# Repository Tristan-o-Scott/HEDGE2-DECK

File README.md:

# HEDGE2-DECK
DECK board for HEDGE-2

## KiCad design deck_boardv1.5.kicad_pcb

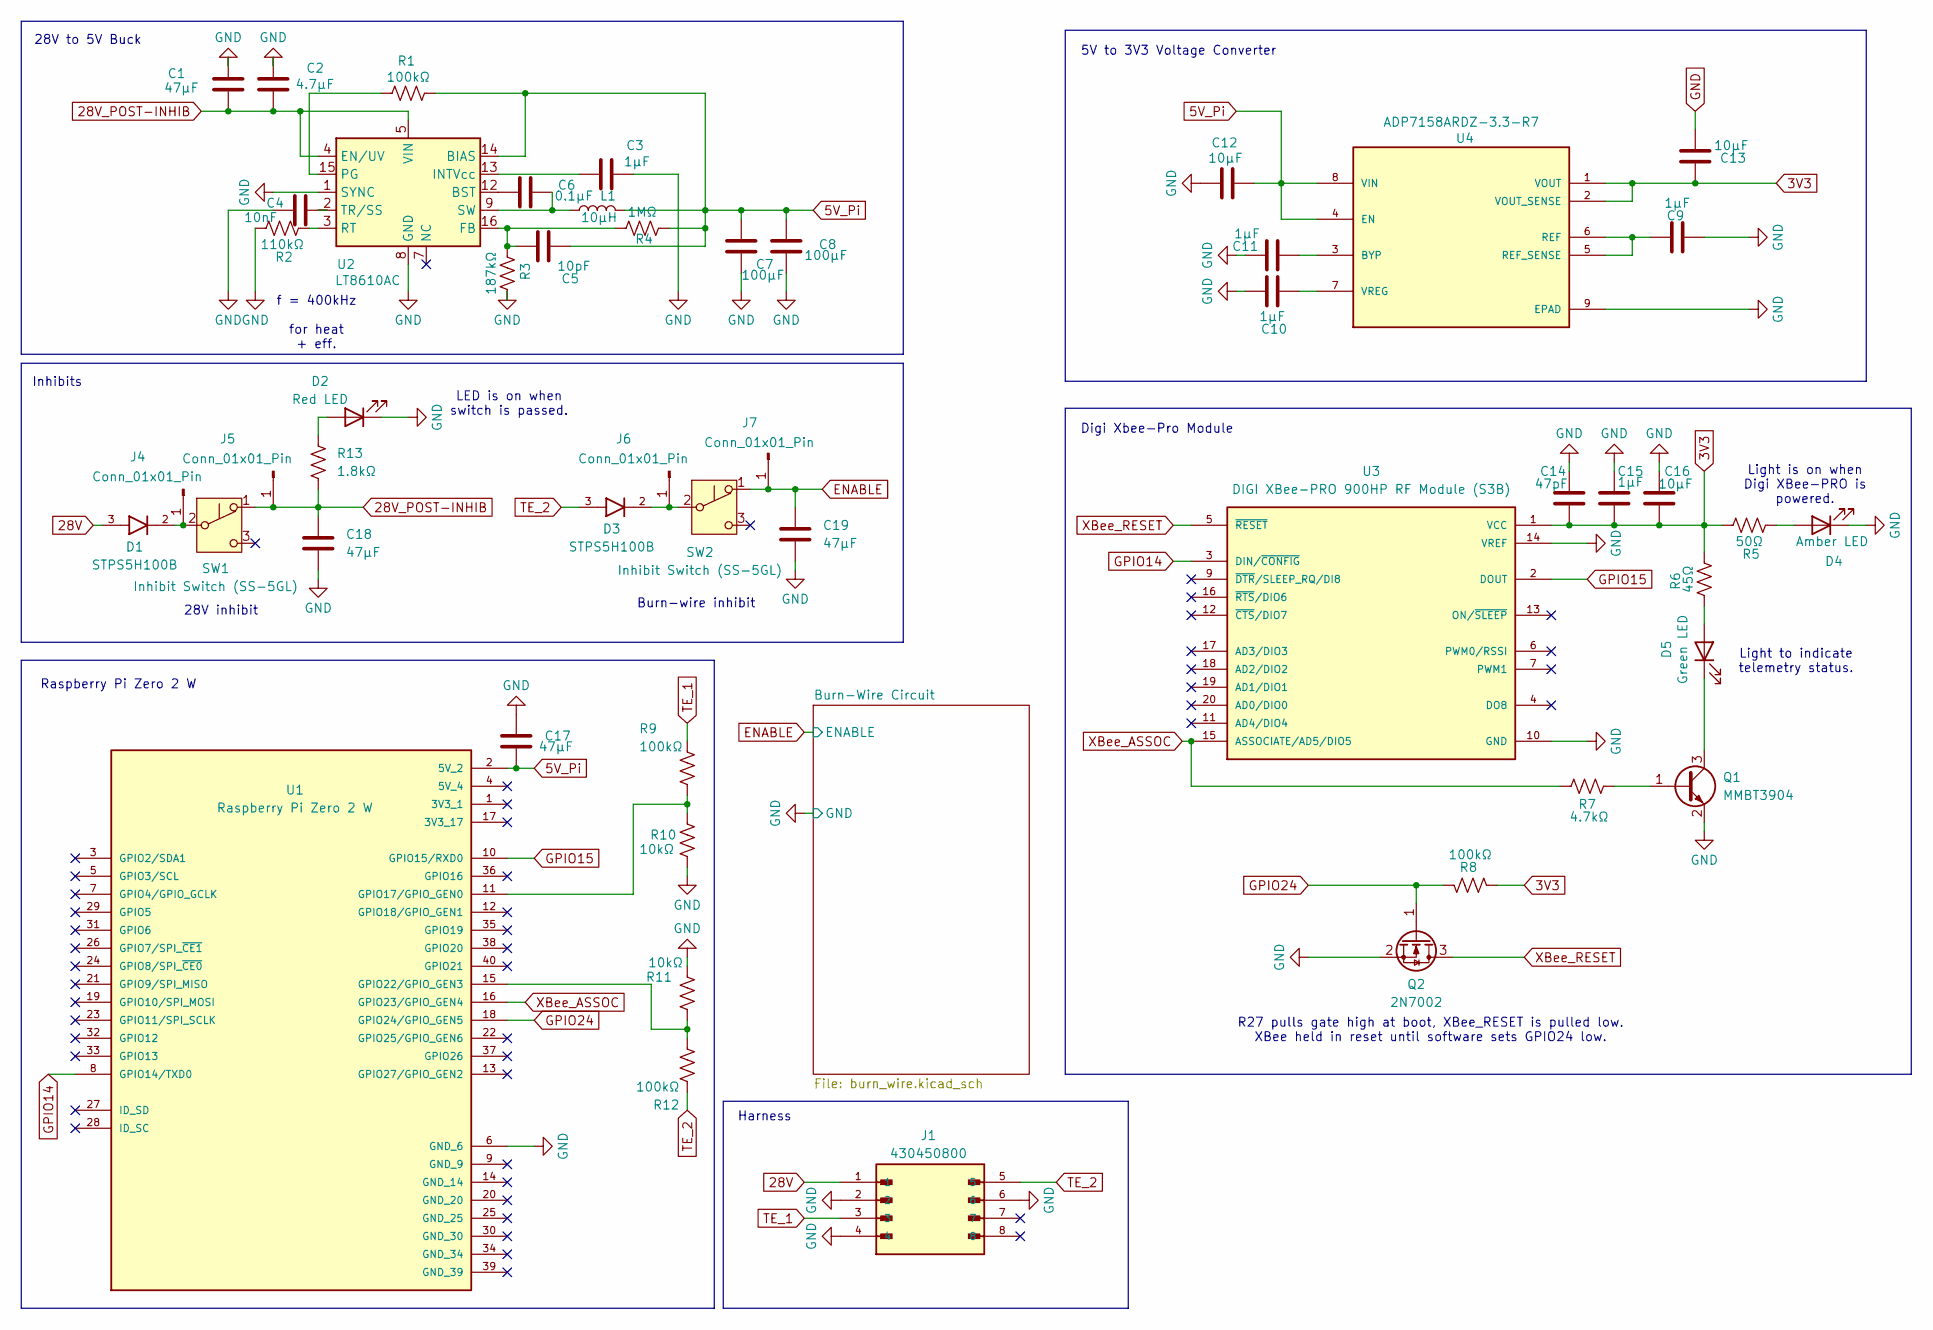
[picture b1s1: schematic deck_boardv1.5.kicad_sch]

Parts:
C1: 47µF; CAP_APZ_1012_KAV
C2: 4.7µF; C_0603_1608Metric
C3, C9, C10, C11, C15: 1µF; C_0603_1608Metric
C4: 10nF; C_0603_1608Metric
C5: 10pF; C_0603_1608Metric
C6: 0.1µF; C_0603_1608Metric
C7, C8: 100µF; C_0603_1608Metric
C12, C13, C16: 10µF; C_0603_1608Metric
C14: 47pF; C_0603_1608Metric
C17, C18, C19: 47µF; C_0603_1608Metric
D1, D3: STPS5H100B; DPAK
D2: Red LED; LED_D3.0mm
D4: Amber LED; LED_D3.0mm
D5: Green LED; LED_D3.0mm
J1: 430450800; MOLEX_430450800; PARTREV G; DigiKey_Part_Number WM1816-ND
J4, J5, J6, J7: Conn_01x01_Pin; SolderWire-0.75sqmm_1x01_D1.25mm_OD2.3mm
L1: 10µH; L_Vishay_IHLP-2525
Q1: MMBT3904; SOT-23
Q2: 2N7002; SOT-23
R1, R8, R9, R12: 100kΩ; R_0603_1608Metric
R2: 110kΩ; R_0603_1608Metric
R3: 187kΩ; R_0603_1608Metric
R4: 1MΩ; R_0603_1608Metric
R5: 50Ω; R_0603_1608Metric
R6: 45Ω; R_0603_1608Metric
R7: 4.7kΩ; R_0603_1608Metric
R10, R11: 10kΩ; R_0603_1608Metric
R13: 1.8kΩ; R_0603_1608Metric
SW1, SW2: Inhibit Switch (SS-5GL); SS-5GL111
U1: Raspberry Pi Zero 2 W; MODULE_SC1176; PARTREV April 2024; DigiKey_Part_Number 2648-SC1176-ND
U2: LT8610AC; MSOP-16-1EP_3x4.039mm_P0.5mm_EP1.651x2.845mm_ThermalVias
U3: DIGI XBee-PRO 900HP RF Module (S3B); DIP2200W51P200L3294H279Q20P
U4: ADP7158ARDZ-3.3-R7; SOIC127P600X175-9N; PARTREV C

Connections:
3V3: C13.2, C14.1, C15.1, C16.1, R5.2, R6.2, R8.2, U3.1 (VCC), U4.1 (VOUT), U4.2 (VOUT_SENSE)
5V_Pi: C5.1, C7.2, C8.2, C12.2, C17.1, L1.2, R1.2, R4.2, U1.2 (5V_2), U2.14 (BIAS), U4.4 (EN), U4.8 (VIN)
28V: D1.3, J1.1
28V_POST-INHIB: C1.2, C2.2, C18.1, J5.1, R13.2, SW1.1 (A), U2.4 (EN/UV), U2.5 (VIN), U2.6 (VIN)
ENABLE: C19.1, J7.1, SW2.1 (A); also elsewhere on the board
GND: C1.1, C2.1, C3.1, C4.2, C7.1, C8.1, C9.2, C10.1, C11.1, C12.1, C13.1, C14.2, C15.2, C16.2, C17.2, C18.2, C19.2, D2.1 (K), D4.1 (K), J1.2, J1.4, J1.6, Q1.2 (E), Q2.2 (S), R2.2, R3.1, R10.2, R11.2, U1.6 (GND_6), U2.1 (SYNC), U2.8 (GND), U2.17 (GND), U3.10 (GND), U3.14 (VREF), U4.9 (EPAD); also elsewhere on the board
GPIO14: U1.8 (GPIO14/TXD0), U3.3 (DIN/~CONFIG)
GPIO15: U1.10 (GPIO15/RXD0), U3.2 (DOUT)
GPIO24: Q2.1 (G), R8.1, U1.18 (GPIO24/GPIO_GEN5)
unnamed: C6.1, L1.1, U2.9 (SW), U2.10 (SW), U2.11 (SW)
unnamed: D2.2 (A), R13.1
unnamed: D4.2 (A), R5.1
unnamed: D5.2 (A), R6.1
unnamed: D5.1 (K), Q1.3 (C)
unnamed: D1.2, J4.1, SW1.2 (B)
unnamed: D3.2, J6.1, SW2.2 (B)
unnamed: Q1.1 (B), R7.2
unnamed: R9.2, R10.1, U1.11 (GPIO17/GPIO_GEN0)
unnamed: R11.1, R12.2, U1.15 (GPIO22/GPIO_GEN3)
unnamed: C6.2, U2.12 (BST)
unnamed: C5.2, R3.2, R4.1, U2.16 (FB)
unnamed: C3.2, U2.13 (INTVcc)
unnamed: R1.1, U2.15 (PG)
unnamed: R2.1, U2.3 (RT)
unnamed: C4.1, U2.2 (TR/SS)
unnamed: C11.2, U4.3 (BYP)
unnamed: C9.1, U4.5 (REF_SENSE), U4.6 (REF)
unnamed: C10.2, U4.7 (VREG)
TE_1: J1.3, R9.1
TE_2: D3.3, J1.5, R12.1
XBee_ASSOC: R7.1, U1.16 (GPIO23/GPIO_GEN4), U3.15 (ASSOCIATE/AD5/DIO5)
XBee_RESET: Q2.3 (D), U3.5 (~RESET)

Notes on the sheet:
Raspberry Pi Zero 2 W
Light is on when Digi XBee-PRO is powered.
f = 400kHz for heat + eff.
LED is on when switch is passed.
5V to 3V3 Voltage Converter
R27 pulls gate high at boot, XBee_RESET is pulled low. XBee held in reset until software sets GPIO24 low.
Harness
Digi Xbee-Pro Module
28V inhibit
Burn-wire inhibit
28V to 5V Buck
Inhibits
Light to indicate telemetry status.

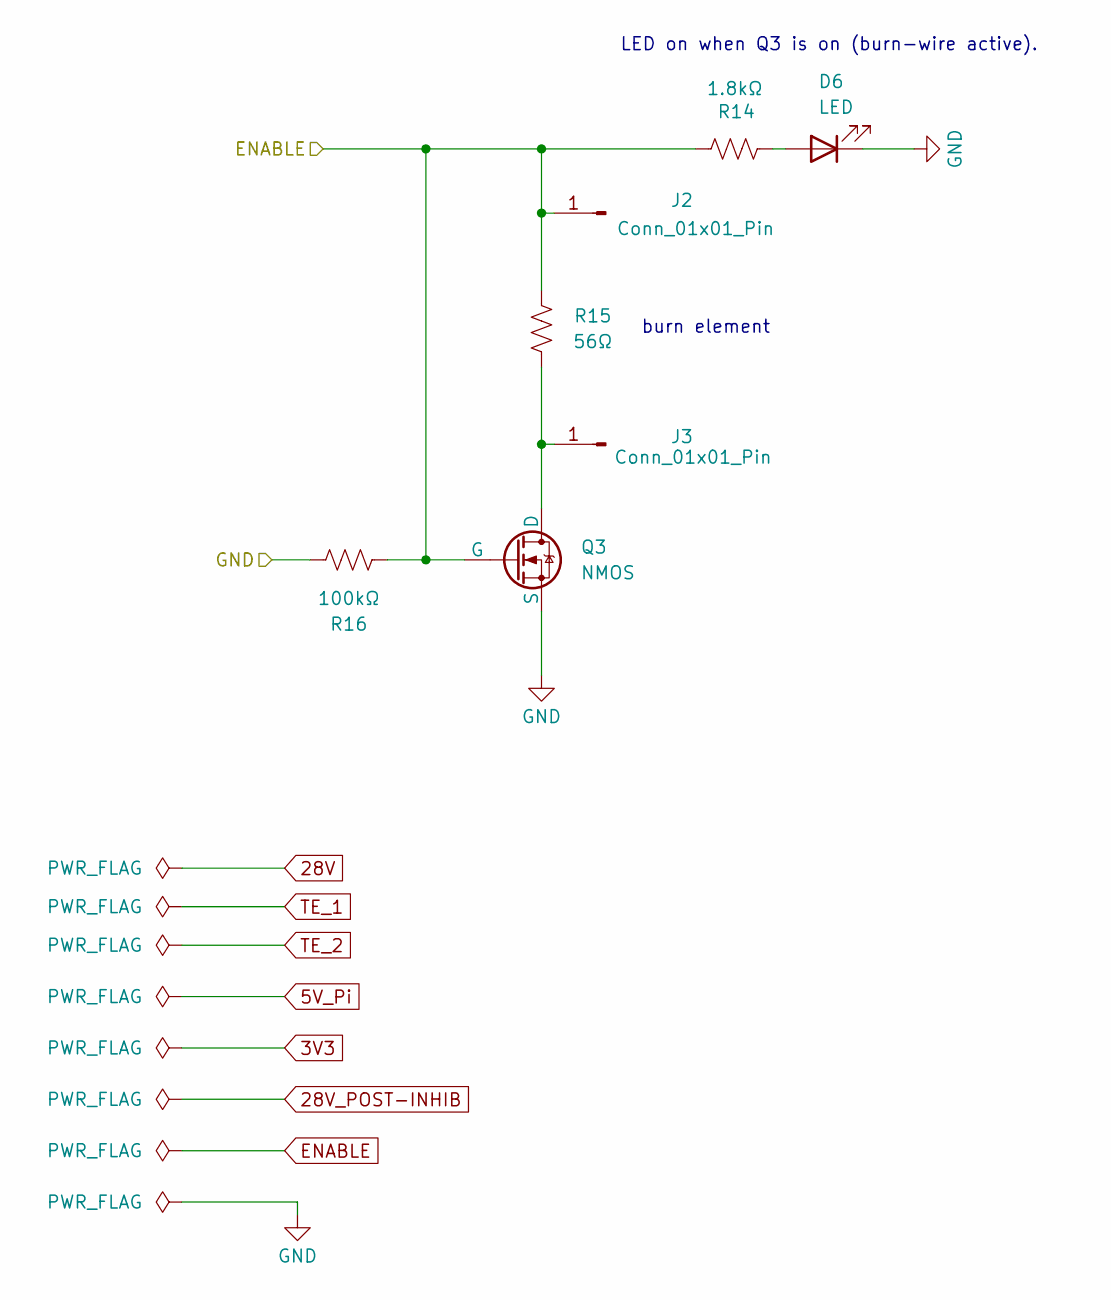
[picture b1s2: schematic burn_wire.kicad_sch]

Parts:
D6: LED; LED_D3.0mm
J2, J3: Conn_01x01_Pin; SolderWire-0.75sqmm_1x01_D1.25mm_OD2.3mm
Q3: NMOS; SOT-23
R14: 1.8kΩ; R_0603_1608Metric
R15: 56Ω; R_0603_1608Metric
R16: 100kΩ; R_0603_1608Metric

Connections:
ENABLE: J2.1, Q3.2 (G), R14.1, R15.2, R16.2; also elsewhere on the board
GND: D6.1 (K), Q3.3 (S), R16.1; also elsewhere on the board
unnamed: D6.2 (A), R14.2
unnamed: J3.1, Q3.1 (D), R15.1

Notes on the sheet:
LED on when Q3 is on (burn-wire active).
burn element

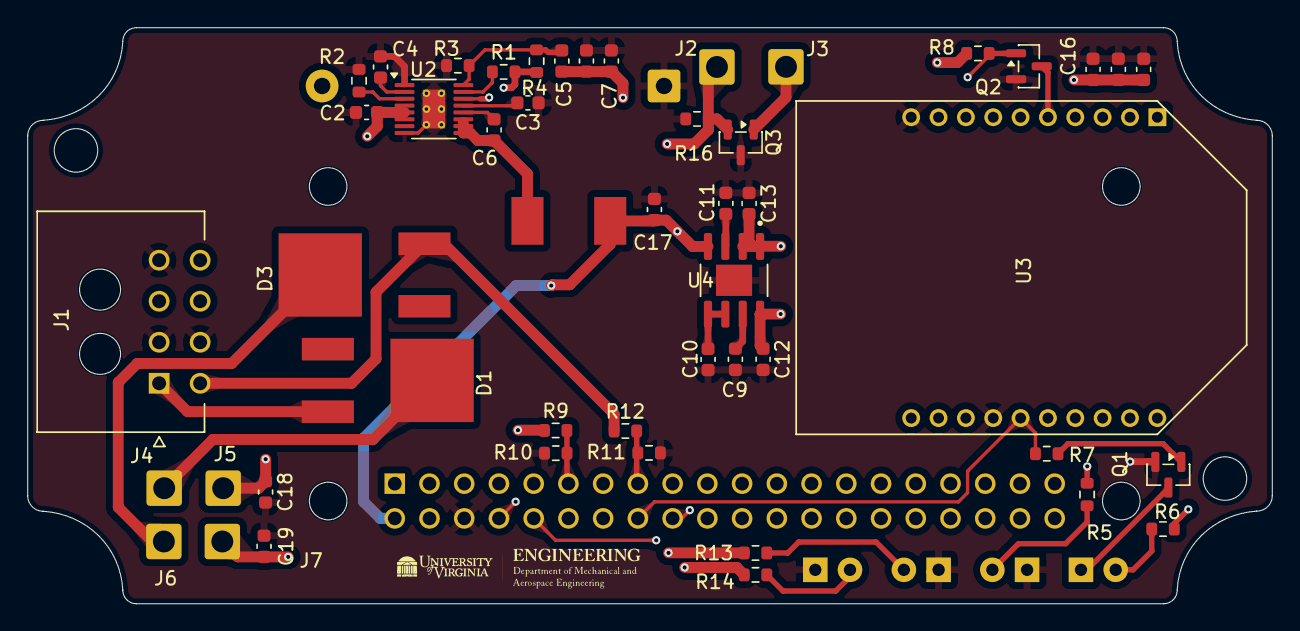
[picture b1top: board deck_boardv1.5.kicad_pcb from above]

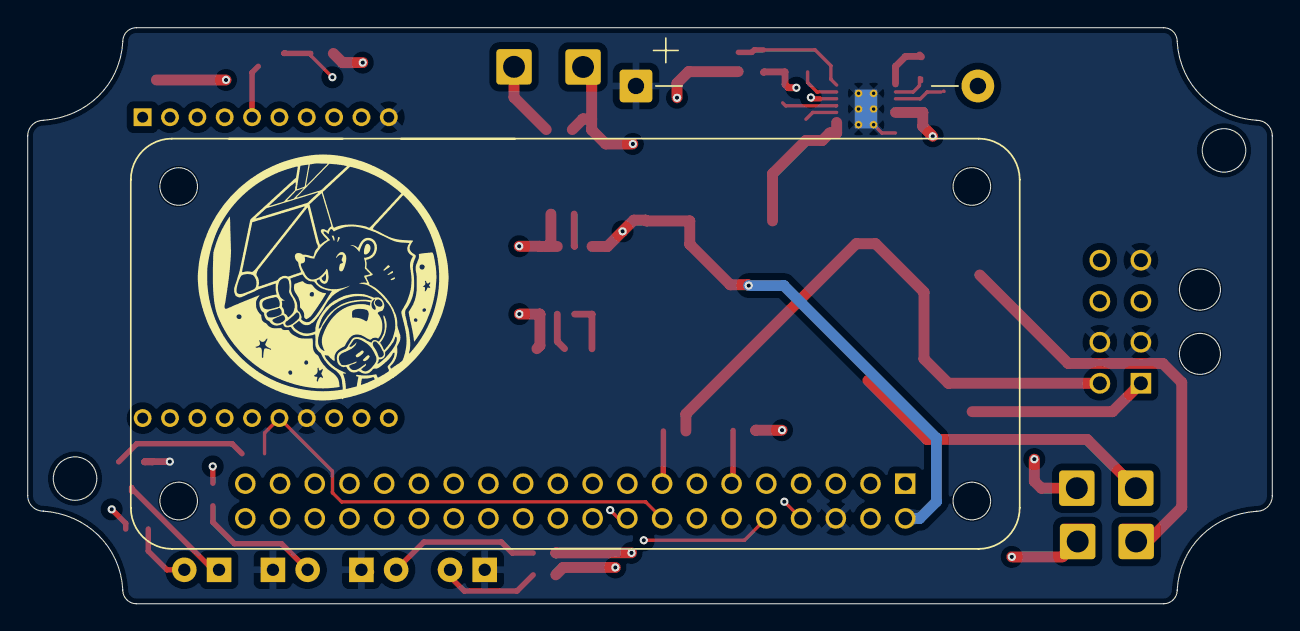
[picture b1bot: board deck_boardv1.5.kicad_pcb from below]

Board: 4 copper layers, 91.0 x 42.1 mm, 55 parts (2 on the bottom side), 34 nets.

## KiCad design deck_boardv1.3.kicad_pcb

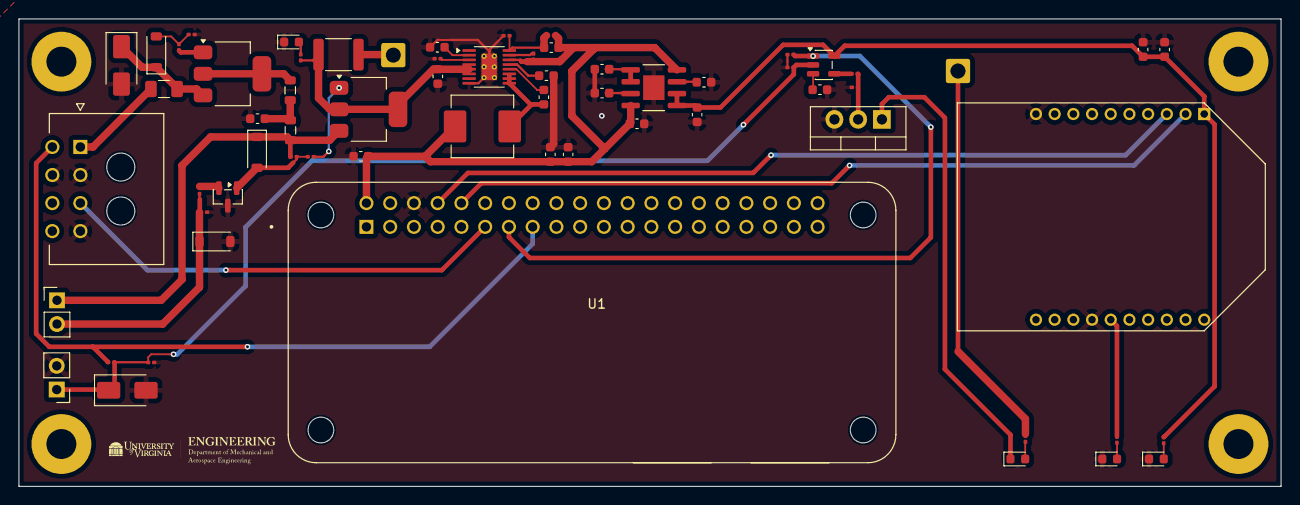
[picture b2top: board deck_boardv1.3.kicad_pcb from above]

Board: 2 copper layers, 135.0 x 50.0 mm, 65 parts (0 on the bottom side), 42 nets.

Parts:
C1: 22 µF; C_0603_1608Metric
C2: 4.7µF; C_0603_1608Metric
C3, C9, C10, C11, C16: 1µF; C_0603_1608Metric
C4: 10nF; C_0603_1608Metric
C5: 10pF; C_0603_1608Metric
C6: 0.1µF; C_0603_1608Metric
C7, C14, C17: 47µF; C_0603_1608Metric
C8, C12: 10µF; C_0603_1608Metric
C13: 0.1 µF; C_0603_1608Metric
C15: 47pF; C_0603_1608Metric
D1: SMAJ36A; D_SMA
D2, D3, D9: BZT52B12; D_SOD-123
D4, D6, D7, D8: LED; LED_0603_1608Metric
D5: 3.6 V Zener; D_SMA
F1: 045101.5; Fuse_1206_3216Metric
F2: 1.0 A; Fuse_1812_4532Metric
J1: 430450800; MOLEX_430450800
J2, J3: Conn_01x01_Pin; SolderWire-0.75sqmm_1x01_D1.25mm_OD2.3mm
L1, L2: 2.2µH; L_0805_2012Metric
L3: 4.7µH; L_Vishay_IHLP-2525
Q1, Q2: FQPF27P06; SOT-223-3_TabPin2
Q3: 2N7000; SOT-23
Q5: NMOS; TO-220-3_Vertical
R1, R3: 100Ω; R_0201_0603Metric
R2, R4, R6, R8, R9, R11, R16, R18, R23: 100kΩ; R_0201_0603Metric
R5, R7, R21, R22: 10kΩ; R_0201_0603Metric
R10: 47Ω; R_0201_0603Metric
R15: 60.4kΩ; R_0201_0603Metric
R17: 412kΩ; R_0201_0603Metric
R19: 1 kΩ; R_0201_0603Metric
R20: 10 kΩ; R_0201_0603Metric
SW1, SW3: SAFE_switch; PinHeader_1x02_P2.54mm_Vertical
U1: Raspberry Pi Zero 2 W; MODULE_SC1176
U2: LT8610AC; MSOP-16-1EP_3x4.039mm_P0.5mm_EP1.651x2.845mm_ThermalVias
U3: DIGI XBee-PRO 900HP RF Module (S3B); XBP24-Z7SIT-004
U4: ADP7159; SOIC127P600X175-9N
U5: 74LVC1G08; SOT-23-5

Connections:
3V3: C8.2, C15.1, C16.1, R19.2, U3.1 (VCC), U4.1 (VOUT), U4.2 (VOUT_SENSE), U5.5 (VCC)
5V_Pi: C5.1, C7.2, C12.2, C14.2, C17.1, L3.2, R17.2, R18.2, U1.2 (5V_2), U2.14 (BIAS), U4.4 (EN), U4.8 (VIN)
/28v_inhibit/28V_Post_Inhibit: C2.2, F2.2, Q2.2 (S), R22.2, U2.4 (EN/UV), U2.5 (VIN), U2.6 (VIN)
/28v_inhibit/28v_IN: F1.1, J1.1
/28v_inhibit/POST_INHIB1: D3.1 (K), L2.2, Q2.3 (D), R4.2, SW1.1 (A)
/Burn-Wire Circuit/CTRL_IN: R9.1, U1.13 (GPIO27-Burn-Wire_Enable), U5.1
/Burn-Wire Circuit/ENABLE: D5.1 (K), R7.1, R8.1, R23.1, SW3.1 (A), U5.2
GND: C1.2, C2.1, C3.1, C4.2, C7.1, C8.1, C9.1, C10.1, C11.1, C12.1, C13.2, C14.1, C15.2, C16.2, C17.2, D1.2 (A2), D4.1 (K), D5.2 (A), D6.1 (K), D8.1 (K), D9.2 (A), J1.2, J1.4, J1.6, Q3.3 (S), Q5.3 (S), R2.2, R6.1, R8.2, R9.2, R11.1, R15.2, R16.1, R23.2, SW3.2 (B), U1.6 (GND_6), U2.8 (GND), U2.17 (GND), U3.10 (GND), U3.14 (VREF), U4.9 (EPAD)
GPIO14: U1.8 (GPIO14/TXD0), U3.3 (DIN/~CONFIG)
GPIO15: U1.10 (GPIO15/RXD0), U3.2 (DOUT)
unnamed: C1.1, L1.2, L2.1
unnamed: C6.1, L3.1, U2.9 (SW), U2.10 (SW), U2.11 (SW)
unnamed: D1.1 (A1), D2.1 (K), F1.2, Q1.3 (D)
unnamed: D2.2 (A), R1.2, R2.1
unnamed: D3.2 (A), Q3.1 (D), R3.2, R4.1
unnamed: D4.2 (A), R22.1
unnamed: D6.2 (A), R19.1
unnamed: D7.2 (A), R21.2
unnamed: D7.1 (K), Q5.1 (D)
unnamed: D8.2 (A), R20.1
unnamed: D9.1 (K), R5.2, R6.2, SW1.2 (B)
unnamed: F2.1, J2.1
unnamed: J3.1, R21.1
unnamed: Q1.1 (G), R1.1
unnamed: L1.1, Q1.2 (S)
unnamed: Q2.1 (G), R3.1
unnamed: Q3.2 (G), R5.1
unnamed: Q5.2 (G), R10.1, R11.2
unnamed: R10.2, U5.4
unnamed: C6.2, U2.12 (BST)
unnamed: C5.2, R16.2, R17.1, U2.16 (FB)
unnamed: C3.2, U2.13 (INTVcc)
unnamed: R18.1, U2.15 (PG)
unnamed: R15.1, U2.3 (RT)
unnamed: C4.1, U2.2 (TR/SS)
unnamed: R20.2, U3.15 (ASSOCIATE/AD5/DIO5)
unnamed: C11.2, U4.3 (BYP)
unnamed: C9.2, U4.5 (REF_SENSE), U4.6 (REF)
unnamed: C10.2, U4.7 (VREG)
unnamed: C13.1, U5.3 (GND)
TE_1: J1.3, U1.11 (GPIO17-Camera_Select)
TE_2: J1.5, R7.2, U1.15 (GPIO22-Deploy_Timer_Input)

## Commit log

2025-11-07 version 1 of the DECK board prior to feedback.
2025-12-03 Edits to board post PDR.
2025-12-04 Updated files and include work done for PCB
2025-12-04 Adjusted PCB so that D-sub and burn-element are off the board.
2026-01-28 PCB is mostly laid out, routing is WIP
2026-01-30 Finished PCB, ready to print
2026-02-02 Made changes to schematic
2026-02-02 Made changes to directory
2026-02-03 adjustments have been made, PCB is also done
2026-02-04 Resolved errors and warnings.
2026-02-06 Resolved manufacturer design rules
2026-02-23 Made board smaller.
2026-02-23 Adjusted components.
2026-02-23 Added labels to silkscreen.
2026-03-03 Made adjustments.
2026-03-27 Fixed footprint sizes.
2026-04-02 Fixed footprints.
2026-04-03 Fixed general issues with footprints.
